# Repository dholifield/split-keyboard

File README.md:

# split-keyboard

- custom reversible PCB using PCA9505 expanders talking to a Seeed XIAO RP2040 over I2C
  - 21 keys per half
- beekeeb SMOLO keycaps
- Kailh x Lofree Ghost switches
- 3D printed case

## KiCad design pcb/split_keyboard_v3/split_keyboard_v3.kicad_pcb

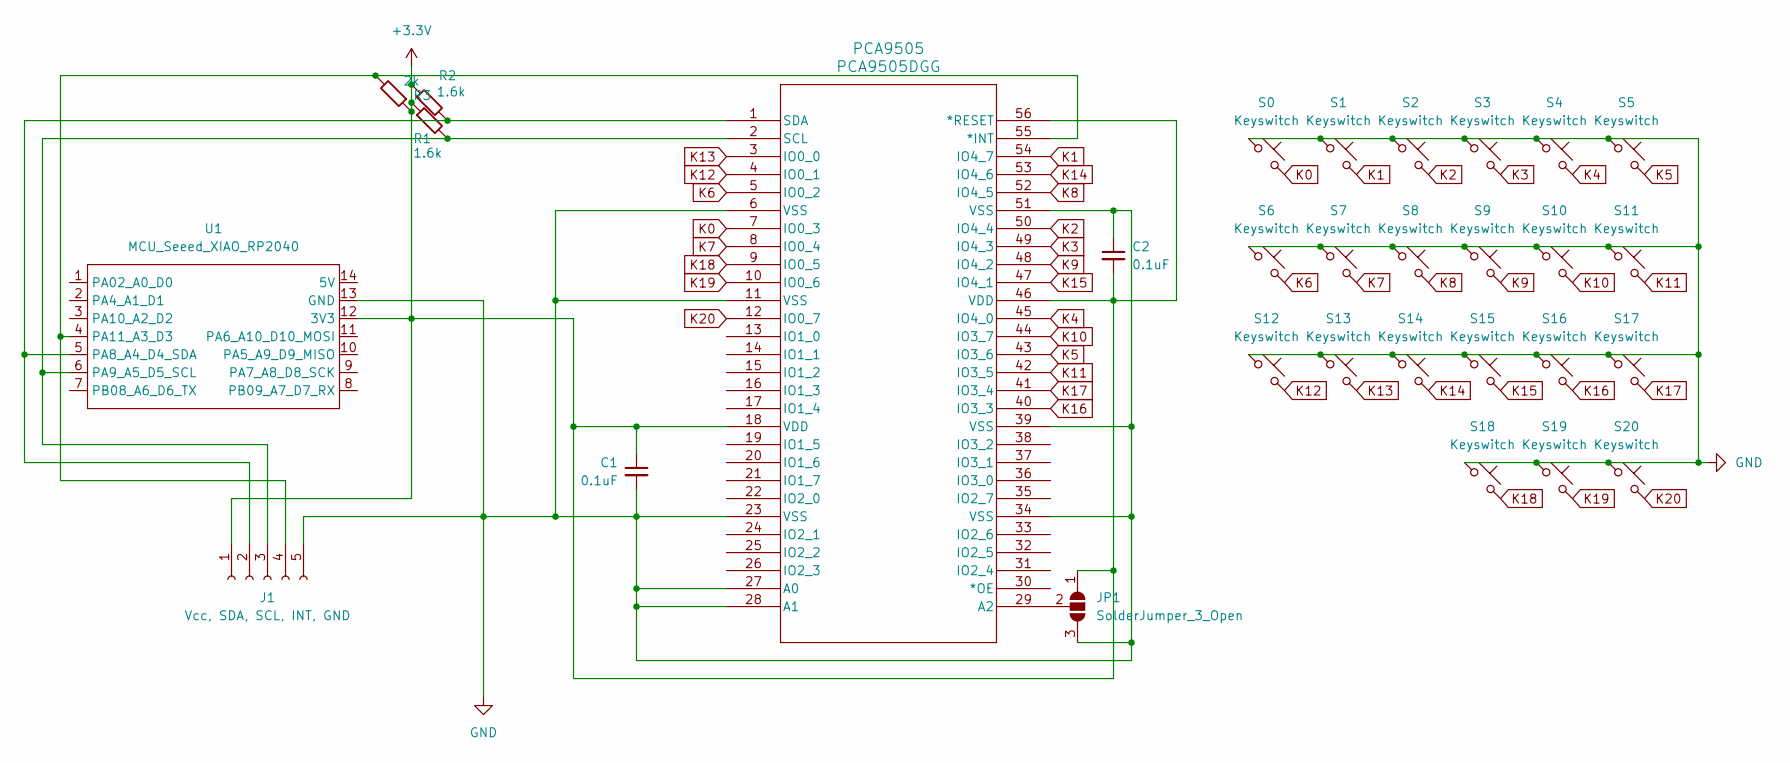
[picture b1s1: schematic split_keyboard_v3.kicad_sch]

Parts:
C1, C2: 0.1uF; C_0603_1608Metric_Pad1.08x0.95mm_HandSolder
J1: Vcc, SDA, SCL, INT, GND; SolderWire-5
JP1: SolderJumper_3_Open; SolderJumper-3_P2.0mm_Open_TrianglePad1.0x1.5mm_NumberLabels
PCA9505: PCA9505DGG; PCA9505
R1, R2: 1.6k; R_0603_1608Metric_Pad0.98x0.95mm_HandSolder
R3: 2k; R_0603_1608Metric_Pad0.98x0.95mm_HandSolder
S0, S1, S2, S3, S4, S5, S6, S7, S8, S9, S10, S11, S12, S13, S14, S15, S16, S17, S18, S19, S20: Keyswitch; Kailh_Low_Profile
U1: MCU_Seeed_XIAO_RP2040; Seeed_XIAO_RP2040

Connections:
+3.3V: C1.1, C2.2, J1.1, JP1.1 (A), PCA9505.18 (VDD), PCA9505.46 (VDD), PCA9505.56 (*RESET), R1.1, R2.1, R3.1, U1.12 (3V3)
GND: C1.2, C2.1, J1.5, JP1.3 (B), PCA9505.6 (VSS), PCA9505.11 (VSS), PCA9505.23 (VSS), PCA9505.27 (A0), PCA9505.28 (A1), PCA9505.34 (VSS), PCA9505.39 (VSS), PCA9505.51 (VSS), S0.1, S1.1, S2.1, S3.1, S4.1, S5.1, S6.1, S7.1, S8.1, S9.1, S10.1, S11.1, S12.1, S13.1, S14.1, S15.1, S16.1, S17.1, S18.1, S19.1, S20.1, U1.13 (GND)
K0: PCA9505.7 (IO0_3), S0.2
K1: PCA9505.54 (IO4_7), S1.2
K2: PCA9505.50 (IO4_4), S2.2
K3: PCA9505.49 (IO4_3), S3.2
K4: PCA9505.45 (IO4_0), S4.2
K5: PCA9505.43 (IO3_6), S5.2
K6: PCA9505.5 (IO0_2), S6.2
K7: PCA9505.8 (IO0_4), S7.2
K8: PCA9505.52 (IO4_5), S8.2
K9: PCA9505.48 (IO4_2), S9.2
K10: PCA9505.44 (IO3_7), S10.2
K11: PCA9505.42 (IO3_5), S11.2
K12: PCA9505.4 (IO0_1), S12.2
K13: PCA9505.3 (IO0_0), S13.2
K14: PCA9505.53 (IO4_6), S14.2
K15: PCA9505.47 (IO4_1), S15.2
K16: PCA9505.40 (IO3_3), S16.2
K17: PCA9505.41 (IO3_4), S17.2
K18: PCA9505.9 (IO0_5), S18.2
K19: PCA9505.10 (IO0_6), S19.2
K20: PCA9505.12 (IO0_7), S20.2
unnamed: J1.2, PCA9505.1 (SDA), R2.2, U1.5 (PA8_A4_D4_SDA)
unnamed: J1.3, PCA9505.2 (SCL), R1.2, U1.6 (PA9_A5_D5_SCL)
unnamed: J1.4, PCA9505.55 (*INT), R3.2, U1.4 (PA11_A3_D3)
unnamed: JP1.2 (C), PCA9505.29 (A2)

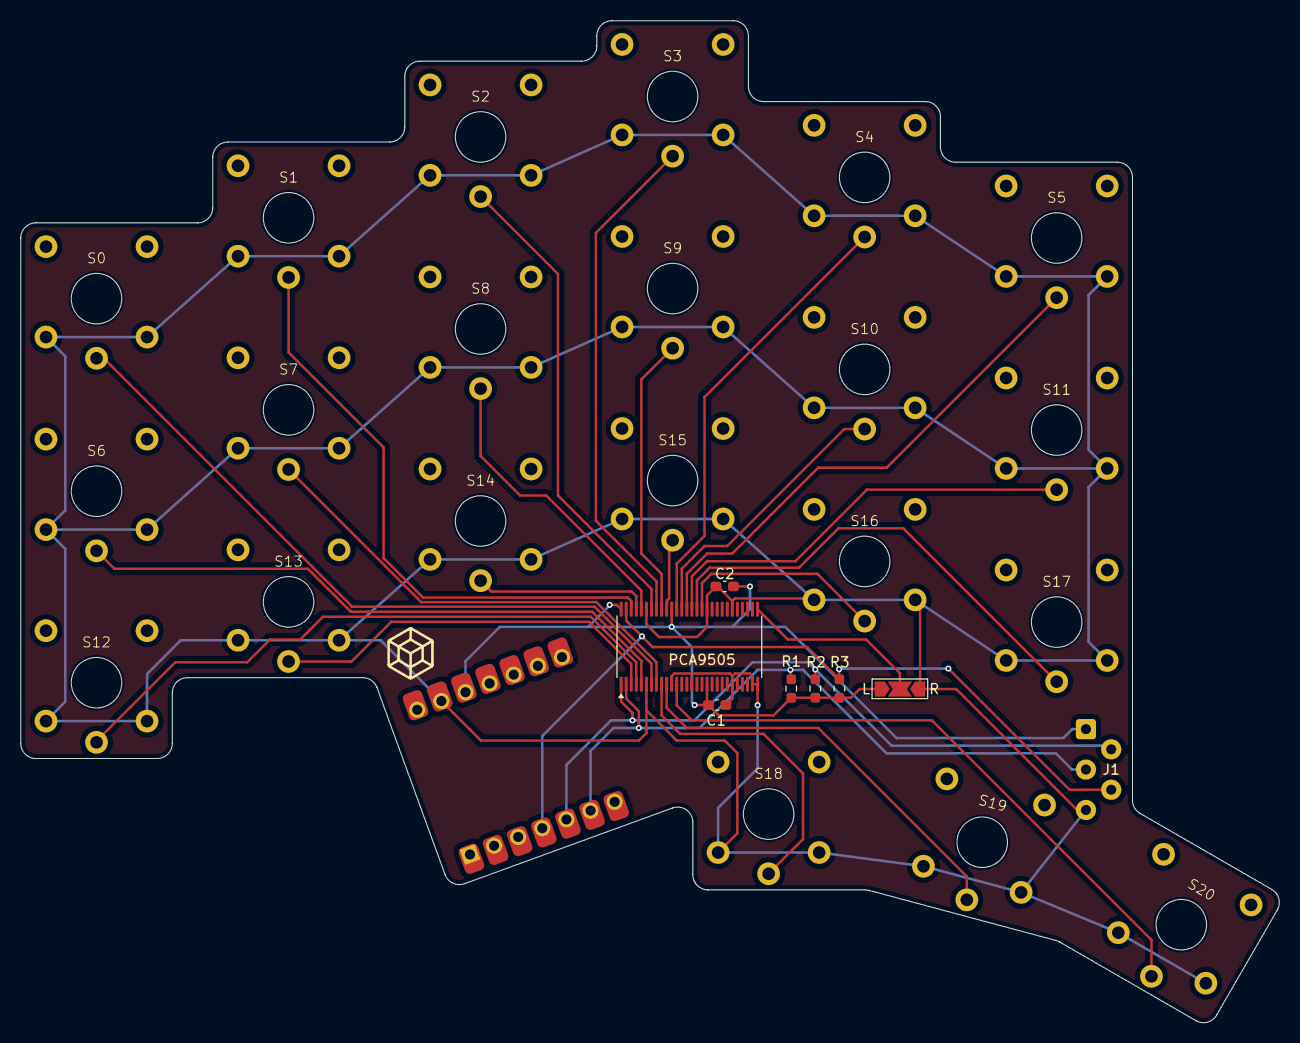
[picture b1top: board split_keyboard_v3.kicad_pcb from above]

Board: 2 copper layers, 124.5 x 99.1 mm, 30 parts (0 on the bottom side), 27 nets.

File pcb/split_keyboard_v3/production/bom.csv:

Designator,Footprint,Quantity,Value,LCSC Part #
"C1, C2",0603,2,0.1uF,
J1,SolderWire-5,1,"Vcc, SDA, SCL, INT, GND",
PCA9505,PCA9505,1,PCA9505DGG,
"R1, R2",0603,2,1.6k,
R3,0603,1,2k,
"S0, S1, S10, S11, S12, S13, S14, S15, S16, S17, S18, S19, S2, S20, S3, S4, S5, S6, S7, S8, S9",Kailh_Low_Profile,21,Keyswitch,
U1,Seeed_XIAO_RP2040,1,MCU_Seeed_XIAO_RP2040,

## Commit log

2025-05-06 initial firmware (WIP)
2025-05-06 add stuff to main
2025-05-07 add keymap - add auto-increment for pca9505
2025-05-08 add qmk firmware - who knows if it works
2025-06-14 add pcb
2025-06-25 add arduino code
2025-06-25 add tinyusb
2025-08-08 add firmware and images
2025-08-09 add full firmware
2026-02-13 rehaul layout
